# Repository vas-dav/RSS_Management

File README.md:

# RoomStateSensor-Management

### Explanation:
This project was made for one reason: to notify my rommmate about my availability. I built an easy circuit using Elegoo Uno and several sensors and  thought to present it to my teacher as an cplusplus project, which later on was declined as it is. Teacher, on the other hand suggested to add several features 
to it, so it would be acceptable for the particular course. 

### Features: 
#### [Controller side](https://github.com/vas-dav/RSS_Management/tree/main/RoomyState): 
- User has for states of a room: **Busy;Home;Come;Away** (Can be found in the [file](RoomyState/lcd.cpp))
- Each state is controllable with a **button** included in the circuit
- When the **button** is pressed, it communicates with a [**Counter class**](RoomyState/Counter.h), which has an overflow feature making it really scalable for more 
states added in future. 
- Indicator LED of a particular state for tail-end with a button
- Indicating the current tempreature and humidity
#### [Computer side](https://github.com/vas-dav/RSS_Management/tree/main/RSS_Management):
- Reading the change of the state coming from an Arduino connected via USB
- Loading your configuration **XML** file, see example [here](RSS_Management/cmake-build-debug/config.xml) 
- Logging the state change during the program is running, see example [here](RSS_Management/cmake-build-debug/Log_File.txt) 
- Sending the log file after closing the program with a telegram bot **NOT IMPLEMENTED**

#### Library usage: 
- [SerialPort](https://github.com/kleydon/Mac-SerialPort-Cpp/tree/master/*%20Project/MacSerialPort/SerialPort)

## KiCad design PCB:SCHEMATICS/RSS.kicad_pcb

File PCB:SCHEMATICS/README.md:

# RoomStateSensor-Management Schematics and PCB

## Explanation:
This project was made for one reason: to notify my rommmate about my availability. I built an easy circuit using Elegoo Uno and several sensors and  thought to present it to my teacher as an cplusplus project, which later on was declined as it is. Teacher, on the other hand suggested to add several features 
to it, so it would be acceptable for the particular course. 

## Features: 
### User side
- User has for states of a room: **Busy;Home;Come;Away** (Can be found in the [file](RoomyState/lcd.cpp))
- Each state is controllable with a **button** included in the circuit
- When the **button** is pressed, it communicates with a [**Counter class**](RoomyState/Counter.h), which has an overflow feature making it really scalable for more 
states added in future. 
- Indicator LED of a particular state for tail-end with a button
- Indicating the current tempreature and humidity
#### Schematics:  

#### PCB: 

### Reciever side:
- Shows the DATA on the 1602LCD
#### Schematics:  

#### PCB: 

#### Library usage: 
- [SerialPort](https://github.com/kleydon/Mac-SerialPort-Cpp/tree/master/*%20Project/MacSerialPort/SerialPort)

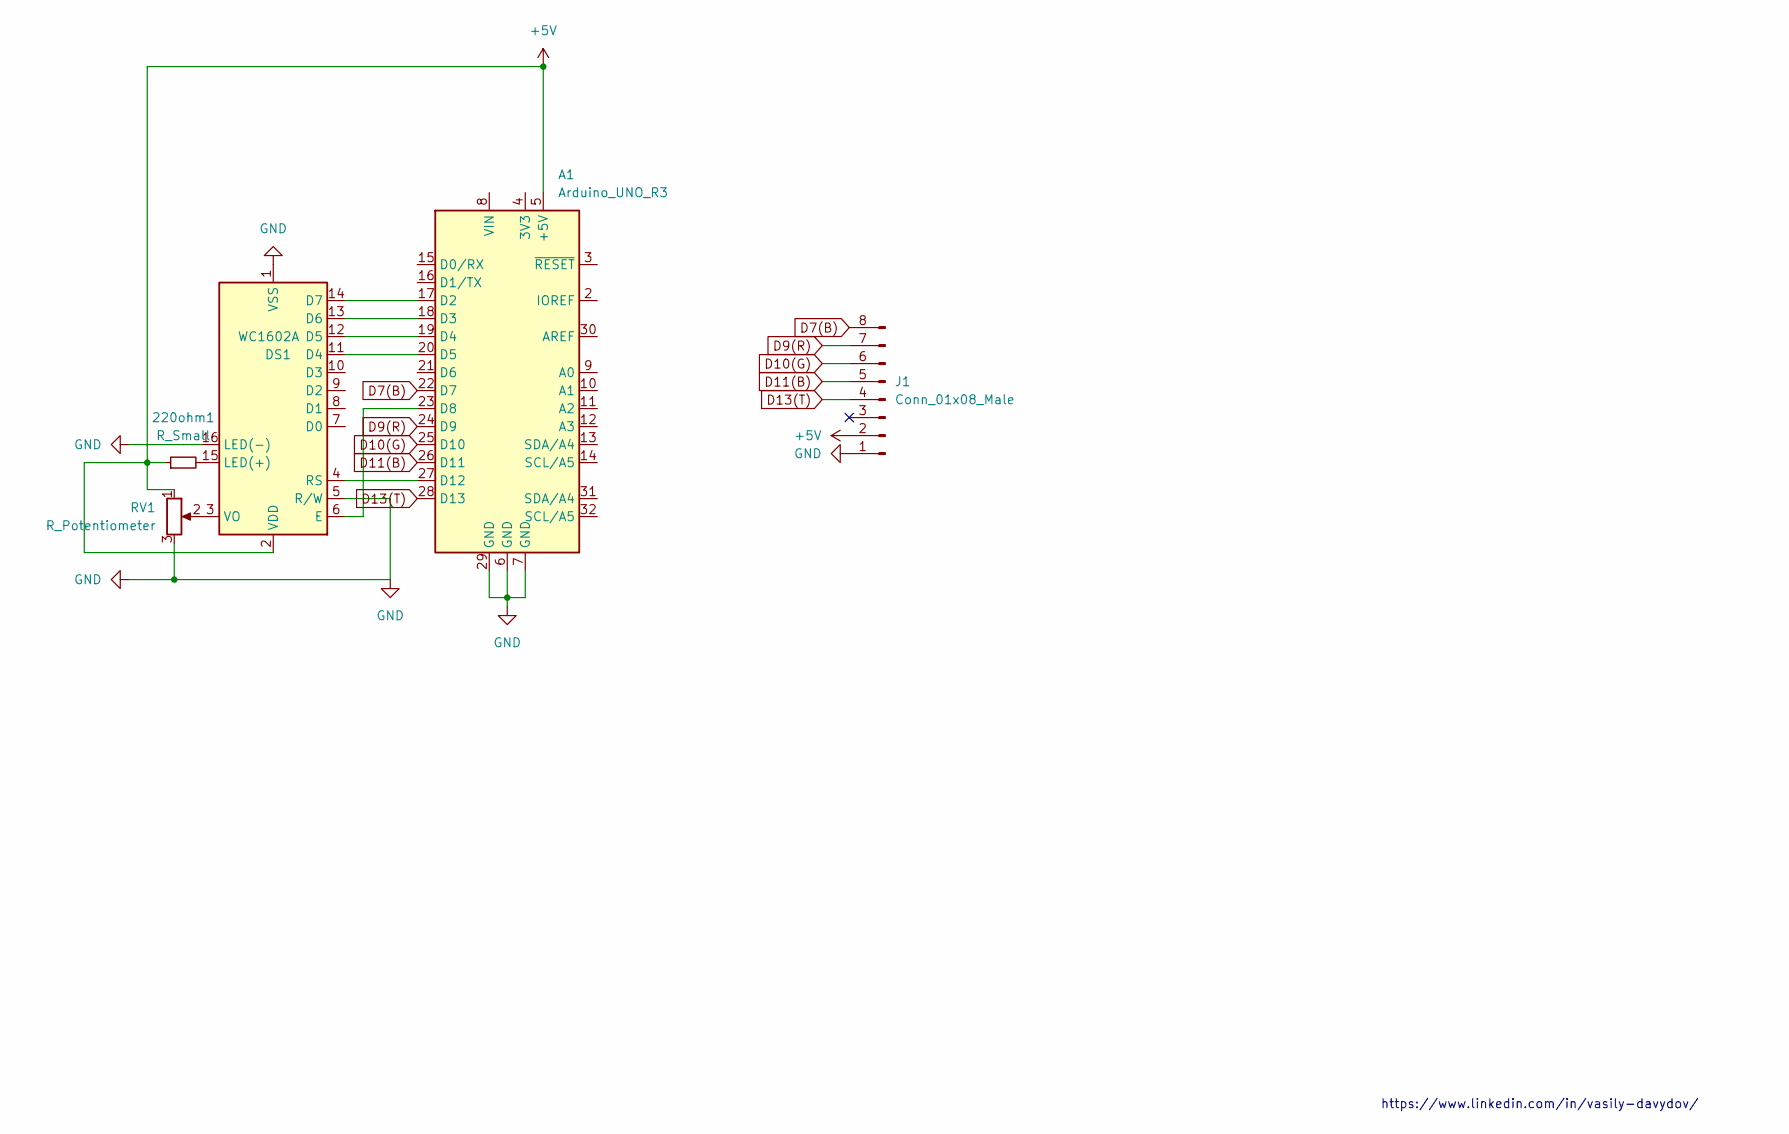
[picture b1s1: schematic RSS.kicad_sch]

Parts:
220ohm1: R_Small; R_Axial_DIN0207_L6.3mm_D2.5mm_P10.16mm_Horizontal
A1: Arduino_UNO_R3
DS1: WC1602A
J1: Conn_01x08_Male; PinHeader_1x08_P2.54mm_Horizontal
RV1: R_Potentiometer; Potentiometer_Piher_PT-15-V15_Vertical

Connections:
+5V: 220ohm1.1, A1.5 (+5V), DS1.2 (VDD), J1.2, RV1.1
D7(B): A1.22 (D7), J1.8
D9(R): A1.24 (D9), J1.7
D10(G): A1.25 (D10), J1.6
D11(B): A1.26 (D11), J1.5
D13(T): A1.28 (D13), J1.4
GND: A1.6 (GND), A1.7 (GND), A1.29 (GND), DS1.1 (VSS), DS1.5 (R/W), DS1.16 (LED(-)), J1.1, RV1.3
unnamed: 220ohm1.2, DS1.15 (LED(+))
unnamed: A1.17 (D2), DS1.14 (D7)
unnamed: A1.18 (D3), DS1.13 (D6)
unnamed: A1.19 (D4), DS1.12 (D5)
unnamed: A1.20 (D5), DS1.11 (D4)
unnamed: A1.23 (D8), DS1.6 (E)
unnamed: A1.27 (D12), DS1.4 (RS)
unnamed: DS1.3 (VO), RV1.2

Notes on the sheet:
https://www.linkedin.com/in/vasily-davydov/

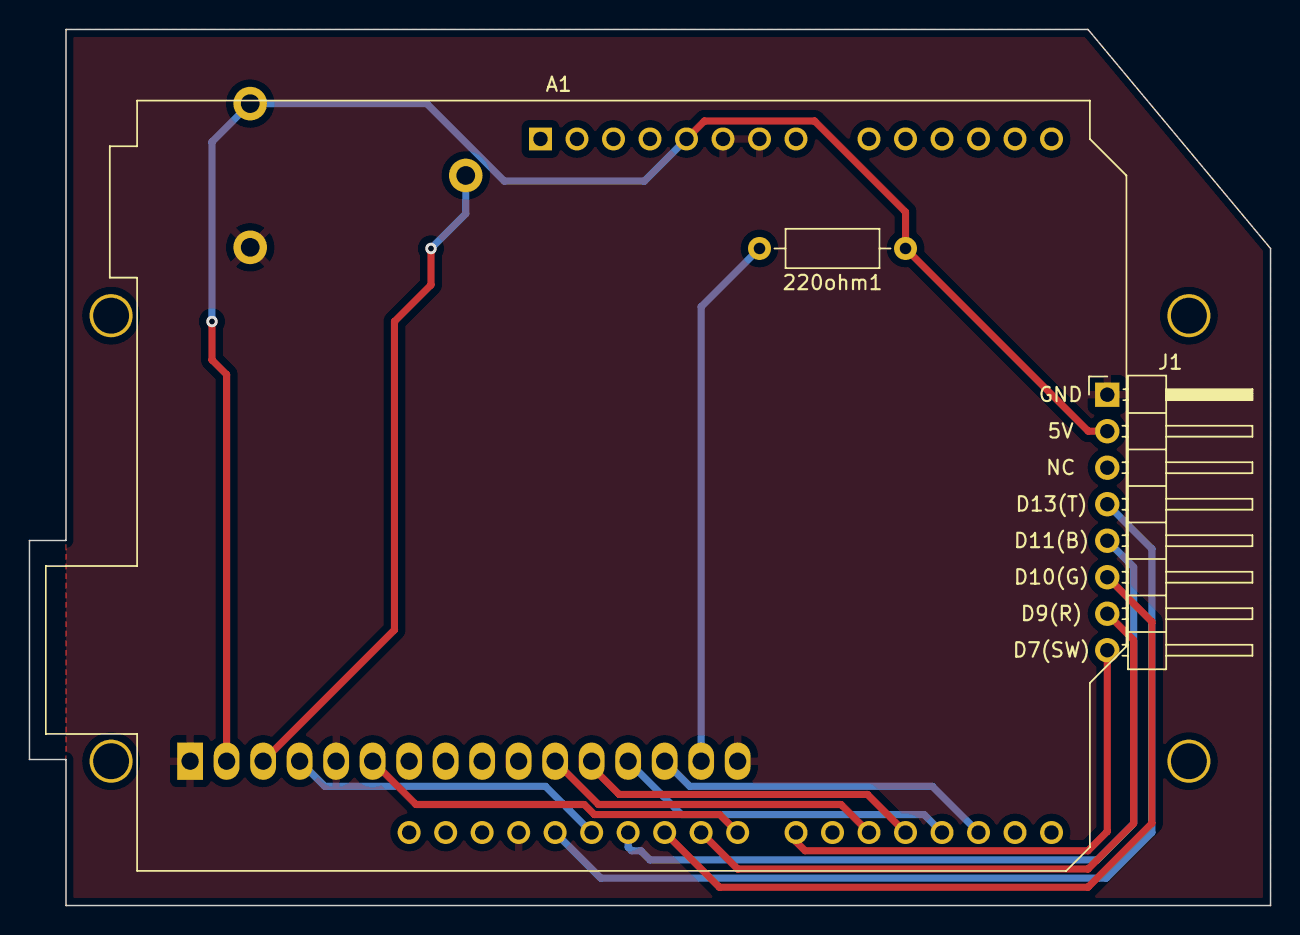
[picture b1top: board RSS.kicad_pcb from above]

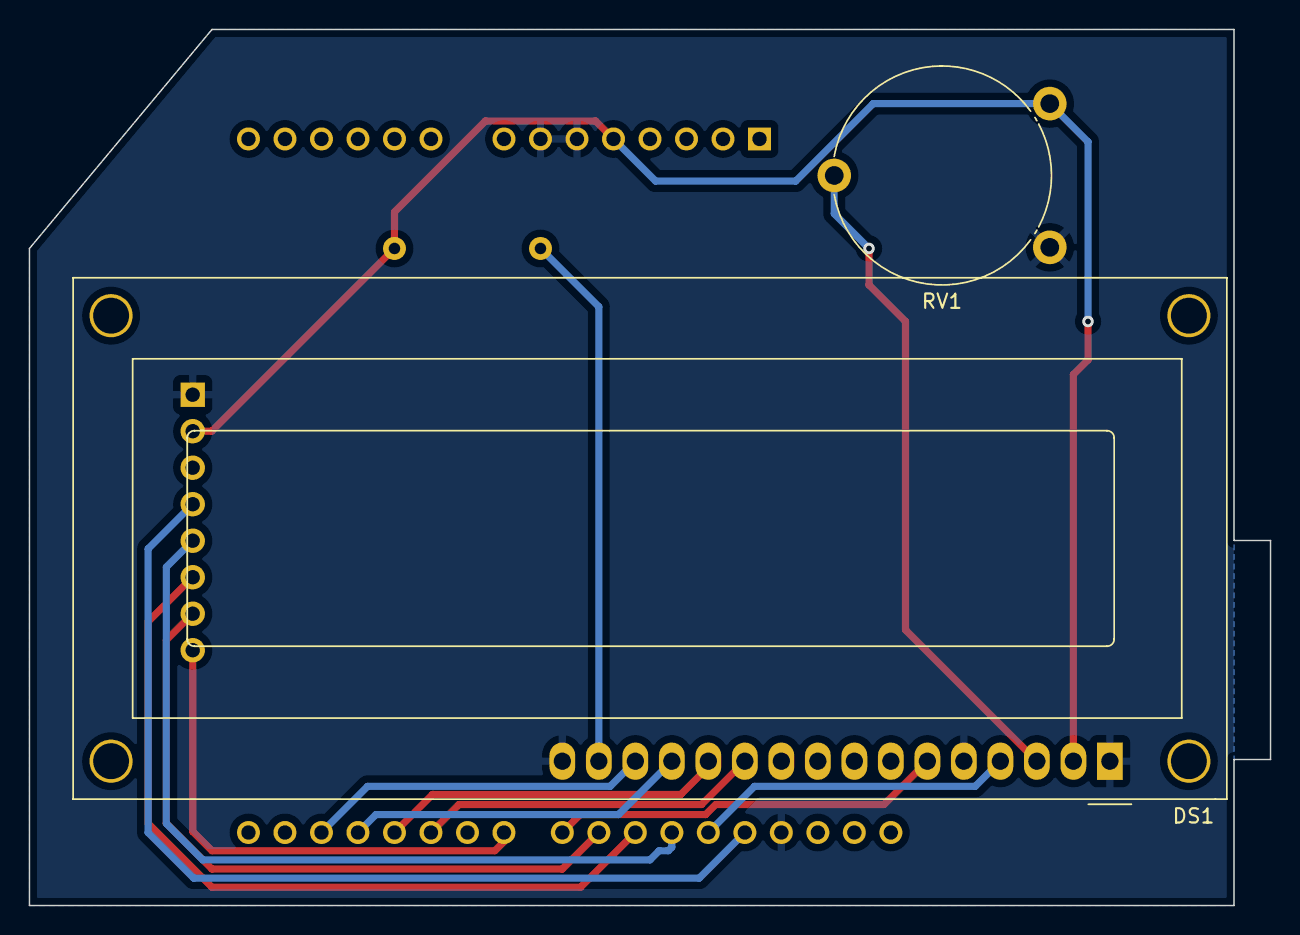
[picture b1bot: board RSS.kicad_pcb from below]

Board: 2 copper layers, 86.4 x 61.0 mm, 5 parts (2 on the bottom side), 15 nets.

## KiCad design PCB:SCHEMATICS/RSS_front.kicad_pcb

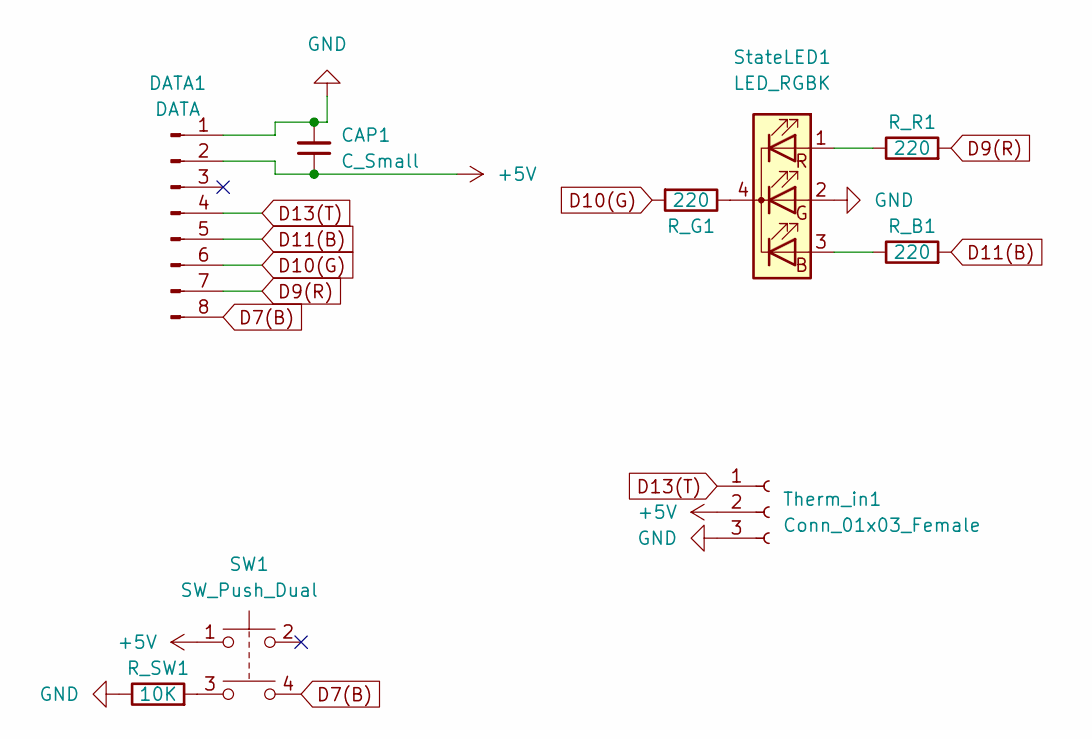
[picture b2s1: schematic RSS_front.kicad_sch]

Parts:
CAP1: C_Small; C_Disc_D4.3mm_W1.9mm_P5.00mm
DATA1: DATA; PinHeader_1x08_P2.54mm_Horizontal
R_B1: 220; R_Axial_DIN0207_L6.3mm_D2.5mm_P10.16mm_Horizontal
R_G1: 220; R_Axial_DIN0207_L6.3mm_D2.5mm_P10.16mm_Horizontal
R_R1: 220; R_Axial_DIN0207_L6.3mm_D2.5mm_P10.16mm_Horizontal
R_SW1: 10K; R_Axial_DIN0207_L6.3mm_D2.5mm_P10.16mm_Horizontal
SW1: SW_Push_Dual; Push_E-Switch_KS01Q01
StateLED1: LED_RGBK; LED_D5.0mm-4_RGB_Wide_Pins
Therm_in1: Conn_01x03_Female; PinSocket_1x03_P2.54mm_Horizontal

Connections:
+5V: CAP1.1, DATA1.2, SW1.1, Therm_in1.2
D7(B): DATA1.8, SW1.4
D9(R): DATA1.7, R_R1.2
D10(G): DATA1.6, R_G1.2
D11(B): DATA1.5, R_B1.2
D13(T): DATA1.4, Therm_in1.1
GND: CAP1.2, DATA1.1, R_SW1.1, StateLED1.2 (GA), Therm_in1.3
unnamed: R_B1.1, StateLED1.3 (BA)
unnamed: R_SW1.2, SW1.3
unnamed: R_R1.1, StateLED1.1 (RA)
unnamed: R_G1.1, StateLED1.4 (K)

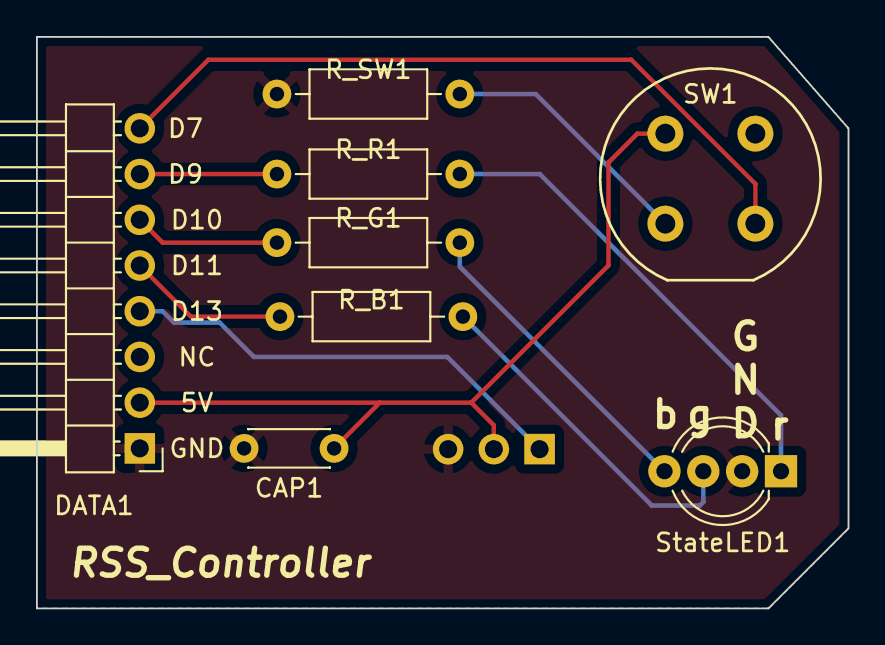
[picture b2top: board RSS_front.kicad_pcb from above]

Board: 2 copper layers, 45.1 x 31.8 mm, 9 parts (1 on the bottom side), 11 nets.

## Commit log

2022-01-10 Add Files
2022-01-13 Rename READme.md to README.md
2022-01-20 Upload Schematics
2022-01-21 Add Recevier Schematics
2022-01-21 Sender Images
